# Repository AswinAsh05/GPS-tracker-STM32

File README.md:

## 📌 Project Overview

The **GPS Tracker Hardware – STM32F030 + SIM808** is a compact and production-ready embedded hardware design built for real-time location tracking applications.  
This board integrates a **32-bit STM32F030 microcontroller**, **SIM808 GSM+GPS module**, and a **wide-input power supply** on a **4-layer PCB** optimized for signal integrity, RF stability, and robust field performance.

This project demonstrates complete hardware engineering including:
- Full schematic development  
- RF-aware PCB routing  
- Power integrity optimization  
- SIM interface & protection circuitry  
- High-quality 3D modeling  
- Manufacturing-ready outputs (Gerber, Drill, STEP)

This repository provides everything required to **study, modify, manufacture, and extend** the hardware.

---

## 📷 PCB & 3D Model Previews

### 🔹 3D Model – Front View  

### 🔹 3D Model – Back View  

---

### 🔹 PCB Layout – Front Layer  
.jpg)

### 🔹 PCB Layout – Back Layer  
.jpg)

---

### 🔹 PCB Layout – Combined View  

---

### 🔹 Schematic Overview

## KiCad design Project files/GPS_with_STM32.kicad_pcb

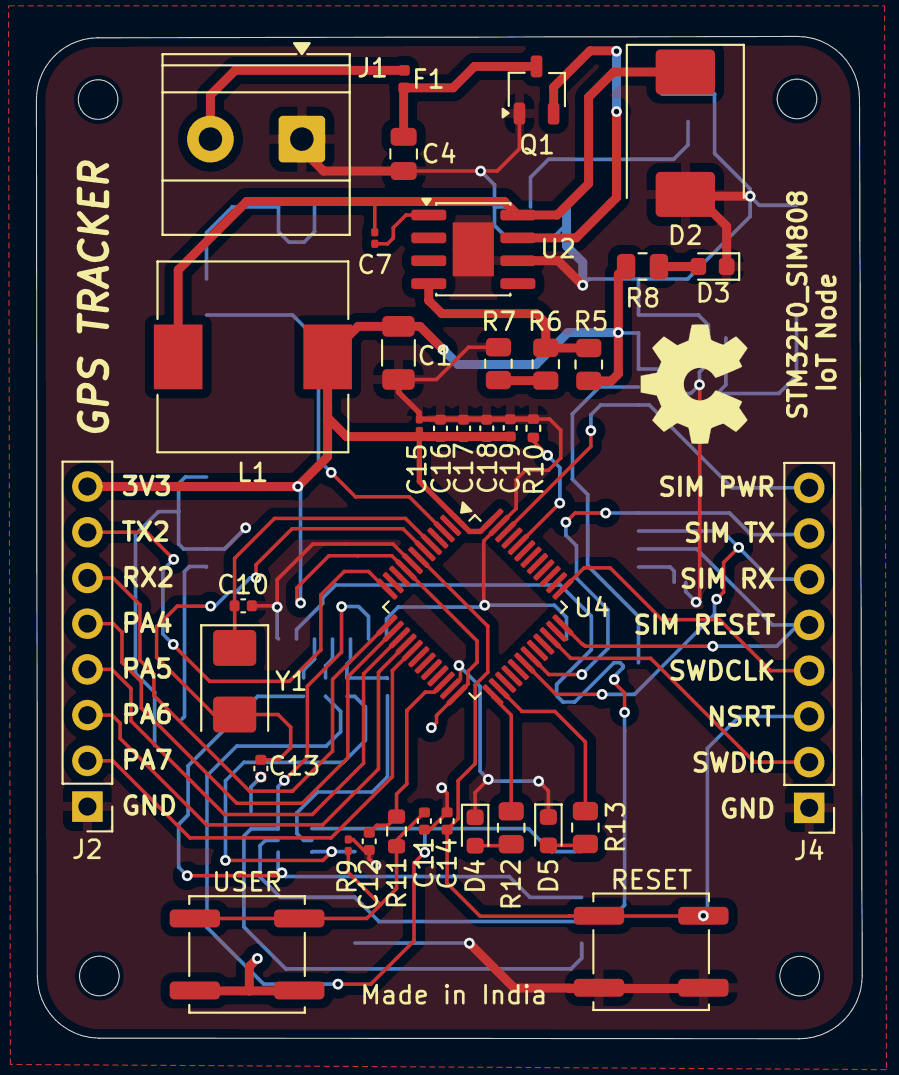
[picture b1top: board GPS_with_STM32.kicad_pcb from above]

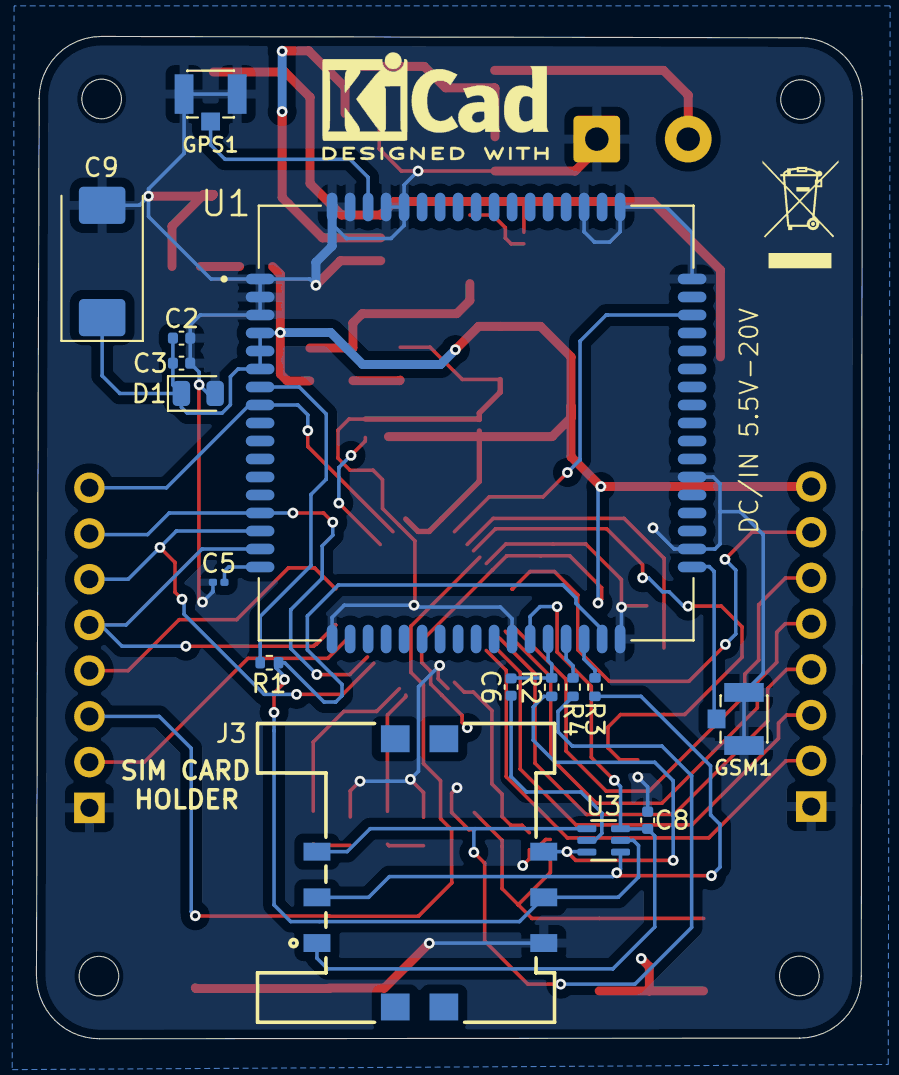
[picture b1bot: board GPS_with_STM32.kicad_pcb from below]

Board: 4 copper layers, 45.9 x 55.7 mm, 57 parts (16 on the bottom side), 46 nets.

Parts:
C1: 100u; C_1206_3216Metric
C2: 33p; C_0402_1005Metric
C3, C11: 10p; C_0402_1005Metric
C4: 10u; C_0805_2012Metric
C5, C15: 4u7; C_0201_0603Metric
C6: 22p; C_0402_1005Metric
C7: 10n; C_0201_0603Metric
C8: 1u; C_0402_1005Metric
C9: 220u; CP_EIA-7343-15_Kemet-W
C10, C13: 30p; C_0402_1005Metric
C12, C14, C16, C17, C18, C19: 100n; C_0402_1005Metric
D1: D_Zener; D_0805_2012Metric
D2: B340; D_SMC
D3, D4, D5: LED; LED_0603_1608Metric
F1: Fuse 2.5A; Fuse_0402_1005Metric
GPS1: U.FL-R-SMT-1
GSM1: U.FL-R-SMT-1
H1, H2, H3, H4: MountingHole; MountingHole_2.2mm_M2
J1: Screw_Terminal_01x02; TerminalBlock_Phoenix_MKDS-1,5-2-5.08_1x02_P5.08mm_Horizont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
J2: Left header pins; PinHeader_1x08_P2.54mm_Vertical
J3: 693010020611
J4: Right header pins; PinHeader_1x08_P2.54mm_Vertical
L1: 15uH; L_10.4x10.4_H4.8
Q1: AO3407A; TSOT-23
R1: 4k7; R_0402_1005Metric
R2, R3, R4, R10: 10k; R_0402_1005Metric
R5: 8k2; R_0805_2012Metric
R6, R8, R12, R13: 1k5; R_0805_2012Metric
R7: 2k7; R_0805_2012Metric
R9: 100k; R_0201_0603Metric
R11: 1k; R_0603_1608Metric
RESET: SW_Push; SW_Push_1P1T_NO_CK_KSC6xxJ
U1: SIM808; XCVR_SIM808
U2: TPS5430DDA; SOIC-8-1EP_3.9x4.9mm_P1.27mm_EP2.29x3mm
U3: SMF05CT1G; SOT65P210X110-6N
U4: STM32F030C8Tx; LQFP-48_7x7mm_P0.5mm
USER: SW_Push; SW_Push_1P1T_NO_CK_KSC6xxJ
Y1: 8MHz; Crystal_SMD_5032-2Pin_5.0x3.2mm

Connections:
+3.3V: C1.1, C2.1, C3.1, C9.1, C15.1, C16.1, C17.1, C18.1, C19.1, D1.1 (K), J2.8, L1.2, R5.1, R8.2, U1.4 (VBAT), U1.5 (VBAT), U1.6 (VBAT), U4.1 (VDD), U4.9 (VDDA), U4.24 (VDD), U4.48 (VDD), USER.2
+12V: F1.1, J1.2
FEEDBACK: R5.2, R6.2, U2.4 (VSENSE)
GND: C1.2, C2.2, C3.2, C4.2, C5.1, C8.1, C9.2, C10.2, C11.2, C12.2, C13.2, C14.1, C15.2, C16.2, C17.2, C18.2, C19.2, D1.2 (A), D2.2 (A), D3.1 (K), D4.1 (K), D5.1 (K), GPS1.GND1, GPS1.GND2, GSM1.GND1, GSM1.GND2, J1.1, J2.1, J3.5 (GND), J4.1, Q1.1 (G), R7.1, R9.1, R10.1, RESET.2, U1.1 (GND), U1.2 (GND), U1.3 (GND), U1.18 (GND), U1.28 (GND), U1.34 (GND), U1.36 (GND), U1.40 (GND), U1.51 (GND), U1.52 (GND), U1.54 (GND), U1.64 (GND), U1.65 (GND), U1.67 (GND), U1.68 (GND), U2.6 (GND), U2.9 (EP), U4.8 (VSSA), U4.23 (VSS), U4.47 (VSS)
GPS_ANT: GPS1.SIG, U1.66 (GSM_ANT)
GSM_ANT: GSM1.SIG, U1.35 (GPS_ANT)
LED1: R12.2, U4.25 (PB12)
LED2: R13.2, U4.26 (PB13)
NSRT: C14.2, J4.3, RESET.1, U4.7 (NRST)
unnamed: C6.2, U3.2
unnamed: C11.1, R9.2, R11.1, USER.1
unnamed: C7.1, D2.1 (K), L1.1, U2.8 (PH)
unnamed: D3.2 (A), R8.1
unnamed: D4.2 (A), R12.1
unnamed: D5.2 (A), R13.1
unnamed: J3.3 (CLK), R4.2, U3.1
unnamed: J3.7 (I/O), R2.2, U3.3
unnamed: J3.2 (RET), R3.2, U3.4
unnamed: C4.1, F1.2, Q1.3 (D)
unnamed: Q1.2 (S), U2.7 (VIN)
unnamed: R6.1, R7.2
unnamed: R1.1, U1.7 (VDD_EXT)
unnamed: C5.2, U1.17 (VRTC)
unnamed: C7.2, U2.1 (BOOT)
unnamed: R10.2, U4.44 (BOOT0)
unnamed: C12.1, R11.2, U4.22 (PB11)
unnamed: C10.1, U4.5 (PF0), Y1.1
unnamed: C13.1, U4.6 (PF1), Y1.2
PA4: J2.5, U4.14 (PA4)
PA5/SPI1_CLK: J2.4, U4.15 (PA5)
PA6/SPI1_MISO: J2.3, U4.16 (PA6)
PA7/SPI1_MOSI: J2.2, U4.17 (PA7)
SIM_CLK: R4.1, U1.31 (SIM_CLK)
SIM_DATA: C6.1, R2.1, U1.30 (SIM_DATA)
SIM_DET: J3.6 (VPP), R1.2, U1.33 (SIM_DET), U3.5
SIM_PWRKEY: J4.8, U1.8 (PWRKEY), U4.46 (PB9)
SIM_RESET: J4.5, U1.16 (~RESET), U4.36 (PF7)
SIM_RST: R3.1, U1.32 (SIM_RST)
SIM_RX: J4.6, U1.15 (RXD), U4.30 (PA9)
SIM_TX: J4.7, U1.14 (TXD), U4.31 (PA10)
SIM_VDD: C8.2, J3.1 (VCC), U1.29 (SIM_VDD), U3.6
STATUS: U1.49 (STATUS), U4.3 (PC14)
SWDCLK: J4.4, U4.37 (PA14)
SWDIO: J4.2, U4.34 (PA13)
USART2_RX: J2.6, U4.13 (PA3)
USART2_TX: J2.7, U4.12 (PA2)

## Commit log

2025-12-11 Enhance README with image previews and formatting
    Updated section headers and added image previews for PCB and 3D models.
2025-12-11 Fix image filenames in README.md
    Updated image filenames in README for consistency.
2025-12-11 Fix image paths in README.md
    Updated image paths in README to use correct casing.
